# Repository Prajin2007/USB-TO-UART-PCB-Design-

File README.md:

# 🔌 USB to UART Converter PCB

A compact USB Type-C to UART converter designed in KiCad, built around the **CP2102N** USB-to-UART bridge IC. Features ESD protection, TX/RX indicator LEDs, and a 5-pin header output.

---

##  Overview

This PCB provides a reliable USB to UART serial interface using Silicon Labs CP2102N. It accepts USB Type-C input and exposes UART signals (TX, RX, RST, VBUS, GND) via a 5-pin header — useful for programming and debugging microcontrollers like STM32, ESP32, and Arduino.

---

## 🔧 Specifications

| Parameter | Value |
|:----------|:------|
| USB Interface | USB Type-C (USB 2.0) |
| Bridge IC | CP2102N-Axx-xQFN28 |
| Output Header | 5-pin (GND, VBUS, RX, TX, RST) |
| ESD Protection | LESD5D5.0CT1G on D+/D- lines |
| TX/RX Indicators | Dual LEDs (D1, D2) |
| CC Resistors | 5.1k (R1, R2) for Type-C detection |
| Decoupling | 100nF caps on VBUS and VDD |
| RST Pull-up | 10k (R3) |
| EDA Tool | KiCad |

---

## 🧠 How It Works

```
USB Type-C Input (J1)
        │
        ├── CC1, CC2 → R1, R2 (5.1k) — USB-C orientation detection
        ├── D+, D-   → ESD diodes (D3, D4, D5) — protection
        │
        ▼
   CP2102N (U1)
   USB-to-UART Bridge IC
        │
        ├── TXD → LED (D1) → TX pin on J2
        ├── RXD → LED (D2) → RX pin on J2
        ├── RST → R3 (10k pull-up) → RST pin on J2
        ├── VBUS → VBUS pin on J2
        └── GND  → GND pin on J2
        │
        ▼
  5-pin Header (J2)
  GND | VBUS | RX | TX | RST
```

1. **USB Type-C receptacle** — modern reversible connector, CC resistors handle orientation
2. **ESD protection** — guards the D+/D- data lines from electrostatic discharge
3. **CP2102N** — handles all USB enumeration and converts USB packets to UART signals
4. **TX/RX LEDs** — blink during data transfer, useful for debugging
5. **5-pin header** — plug directly into target microcontroller UART pins

---

## 🧩 Bill of Materials

| Ref | Component | Value | Package |
|:----|:----------|:------|:--------|
| U1 | USB-UART Bridge | CP2102N-Axx-xQFN28 | QFN-28 |
| J1 | USB Type-C Receptacle | USB2.0 16P | SMD |
| J2 | Pin Header | 5-pin | Conn_01x05 |
| D1, D2 | LED | TX/RX Indicator | SMD |
| D3, D4, D5 | ESD Diode | LESD5D5.0CT1G | SOT-23 |
| R1, R2 | Resistor | 5.1k | 0402 |
| R3 | Resistor | 10k | 0402 |
| R4, R5, R6, R7 | Resistor | Current limit | 0402 |
| C1, C2 | Capacitor | 100nF | 0402 |
| C3, C4 | Capacitor | Decoupling | 0402 |

---

## 🖼️ Screenshots

### Schematic

### PCB Layout

---

## 🔌 Pinout — Output Header (J2)

| Pin | Signal | Description |
|:---:|:-------|:------------|
| 1 | GND | Ground |
| 2 | VBUS | 5V USB Power |
| 3 | RX | UART Receive |
| 4 | TX | UART Transmit |
| 5 | RST | Reset |

---

## 🛠️ Tools Used

---

## 📚 What I Learned

- USB Type-C connector wiring and CC resistor configuration
- CP2102N IC integration and decoupling best practices
- ESD protection placement on high-speed USB data lines
- Compact PCB layout with SMD components
- LED indicator circuit design for TX/RX activity

---

## 👤 Author

**Prajin S**
B.Tech Electronics and Instrumentation Engineering, VIT Vellore

---

*Designed as part of my PCB design learning journey — EIE, VIT Vellore.*

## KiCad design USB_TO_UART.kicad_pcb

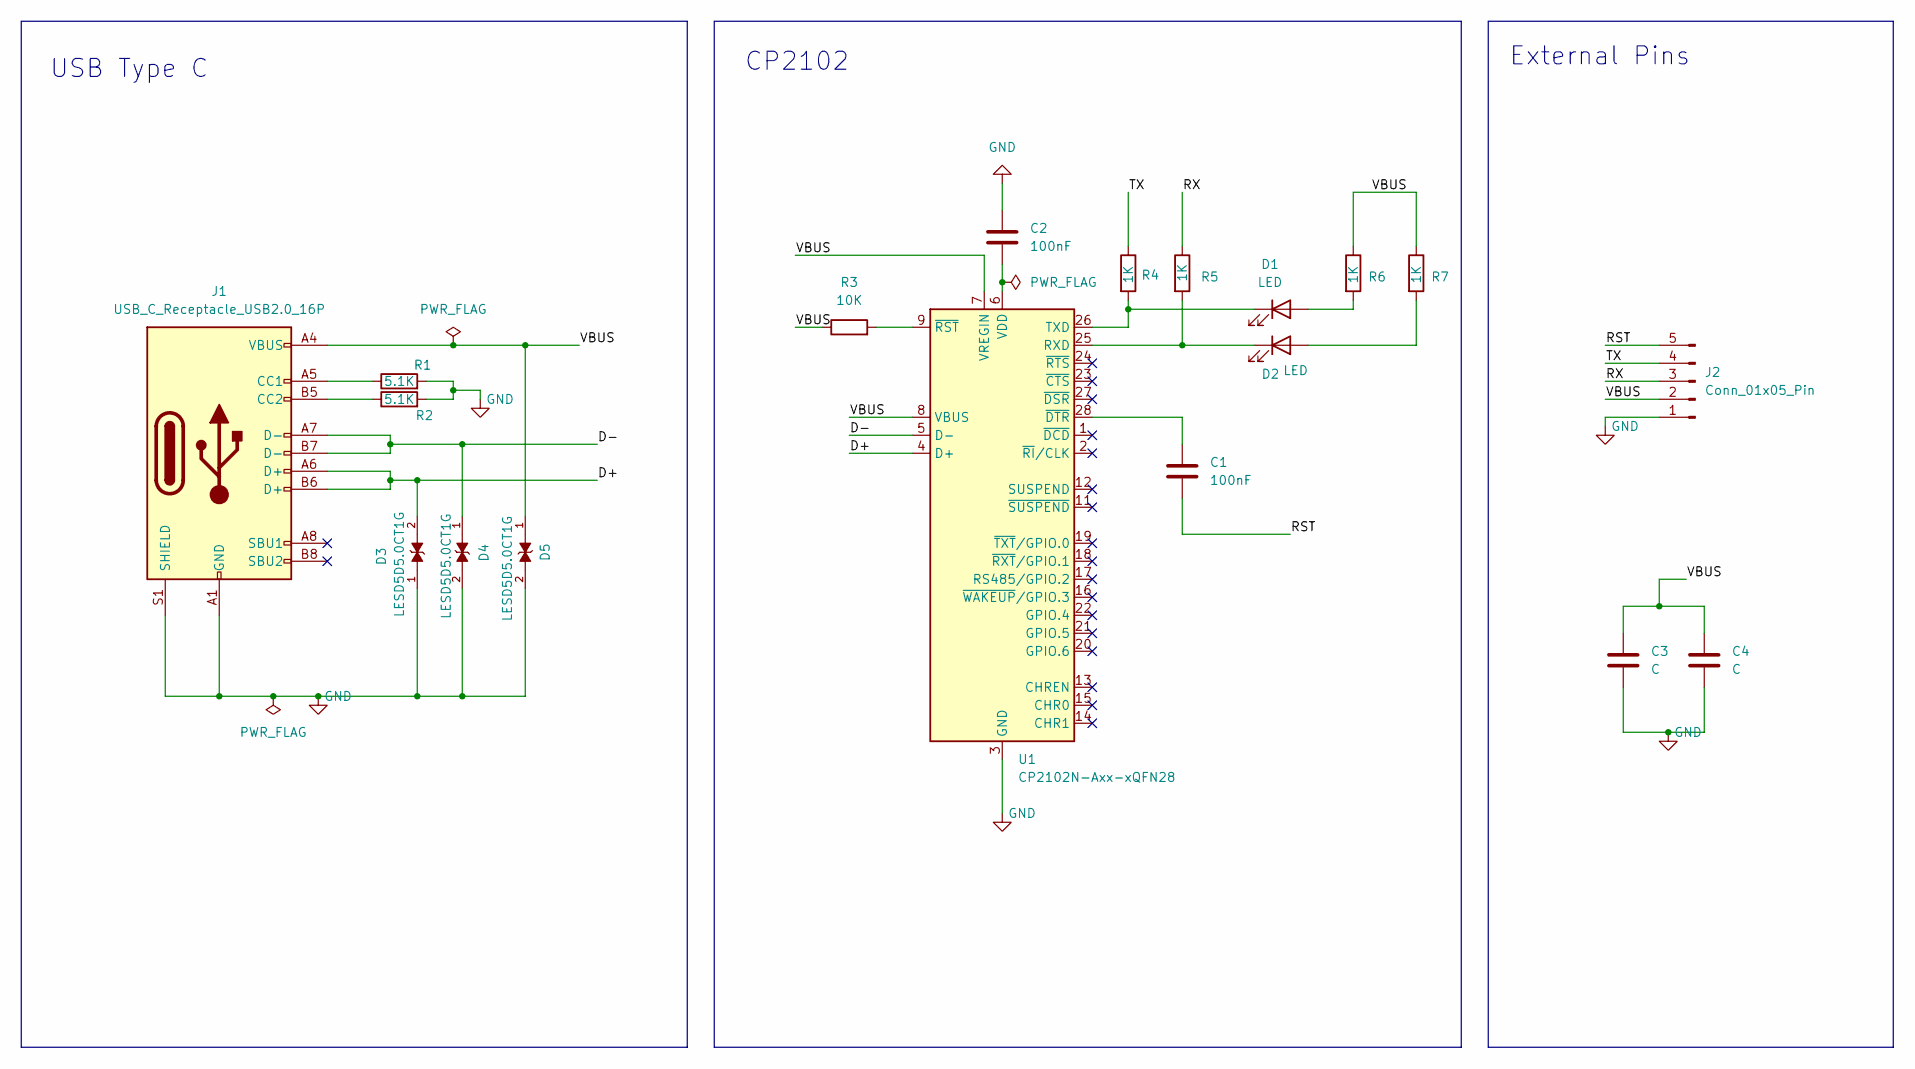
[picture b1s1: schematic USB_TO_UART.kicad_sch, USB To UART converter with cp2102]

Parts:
C1, C2: 100nF; C_0201_0603Metric
C3, C4: C; C_0201_0603Metric
D1, D2: LED; LED_0201_0603Metric
D3, D4, D5: LESD5D5.0CT1G; TVS_LESD5D5.0CT1G; PARTREV O
J1: USB_C_Receptacle_USB2.0_16P; USB_C_Receptacle_HRO_TYPE-C-31-M-12
J2: Conn_01x05_Pin; PinHeader_1x05_P2.54mm_Horizontal
R1, R2: 5.1K; R_0201_0603Metric
R3: 10K; R_0201_0603Metric
R4, R5, R6, R7: 1K; R_0201_0603Metric
U1: CP2102N-Axx-xQFN28; QFN-28-1EP_5x5mm_P0.5mm_EP3.35x3.35mm

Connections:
/D+: D3.2, J1.A6 (D+), J1.B6 (D+), U1.4 (D+)
/D-: D4.1, J1.A7 (D-), J1.B7 (D-), U1.5 (D-)
/RST: C1.2, J2.5
/RX: J2.3, R5.1
/TX: J2.4, R4.1
/VBUS: C3.1, C4.1, D5.1, J1.A4 (VBUS), J1.A9 (VBUS), J1.B4 (VBUS), J1.B9 (VBUS), J2.2, R3.1, R6.1, R7.1, U1.7 (VREGIN), U1.8 (VBUS)
GND: C2.1, C3.2, C4.2, D3.1, D4.2, D5.2, J1.A1 (GND), J1.A12 (GND), J1.B1 (GND), J1.B12 (GND), J1.S1 (SHIELD), J2.1, R1.2, R2.2, U1.3 (GND), U1.29 (GND)
unnamed: D1.2 (A), R6.2
unnamed: D1.1 (K), R4.2, U1.26 (TXD)
unnamed: D2.2 (A), R7.2
unnamed: D2.1 (K), R5.2, U1.25 (RXD)
unnamed: J1.A5 (CC1), R1.1
unnamed: J1.B5 (CC2), R2.1
unnamed: C2.2, U1.6 (VDD)
unnamed: C1.1, U1.28 (~DTR)
unnamed: R3.2, U1.9 (~RST)

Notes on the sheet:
External Pins
USB Type C
CP2102

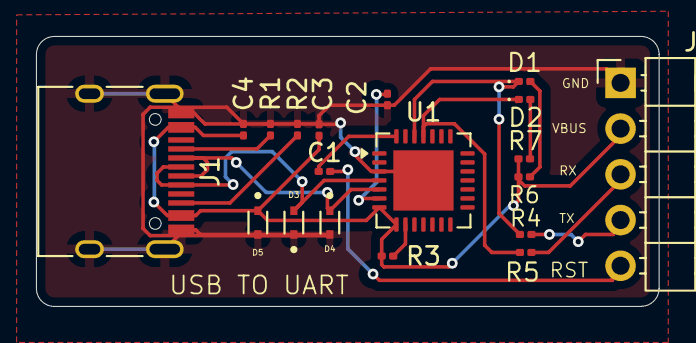
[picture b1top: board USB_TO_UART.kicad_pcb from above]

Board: 2 copper layers, 34.6 x 15.0 mm, 19 parts (0 on the bottom side), 16 nets.
